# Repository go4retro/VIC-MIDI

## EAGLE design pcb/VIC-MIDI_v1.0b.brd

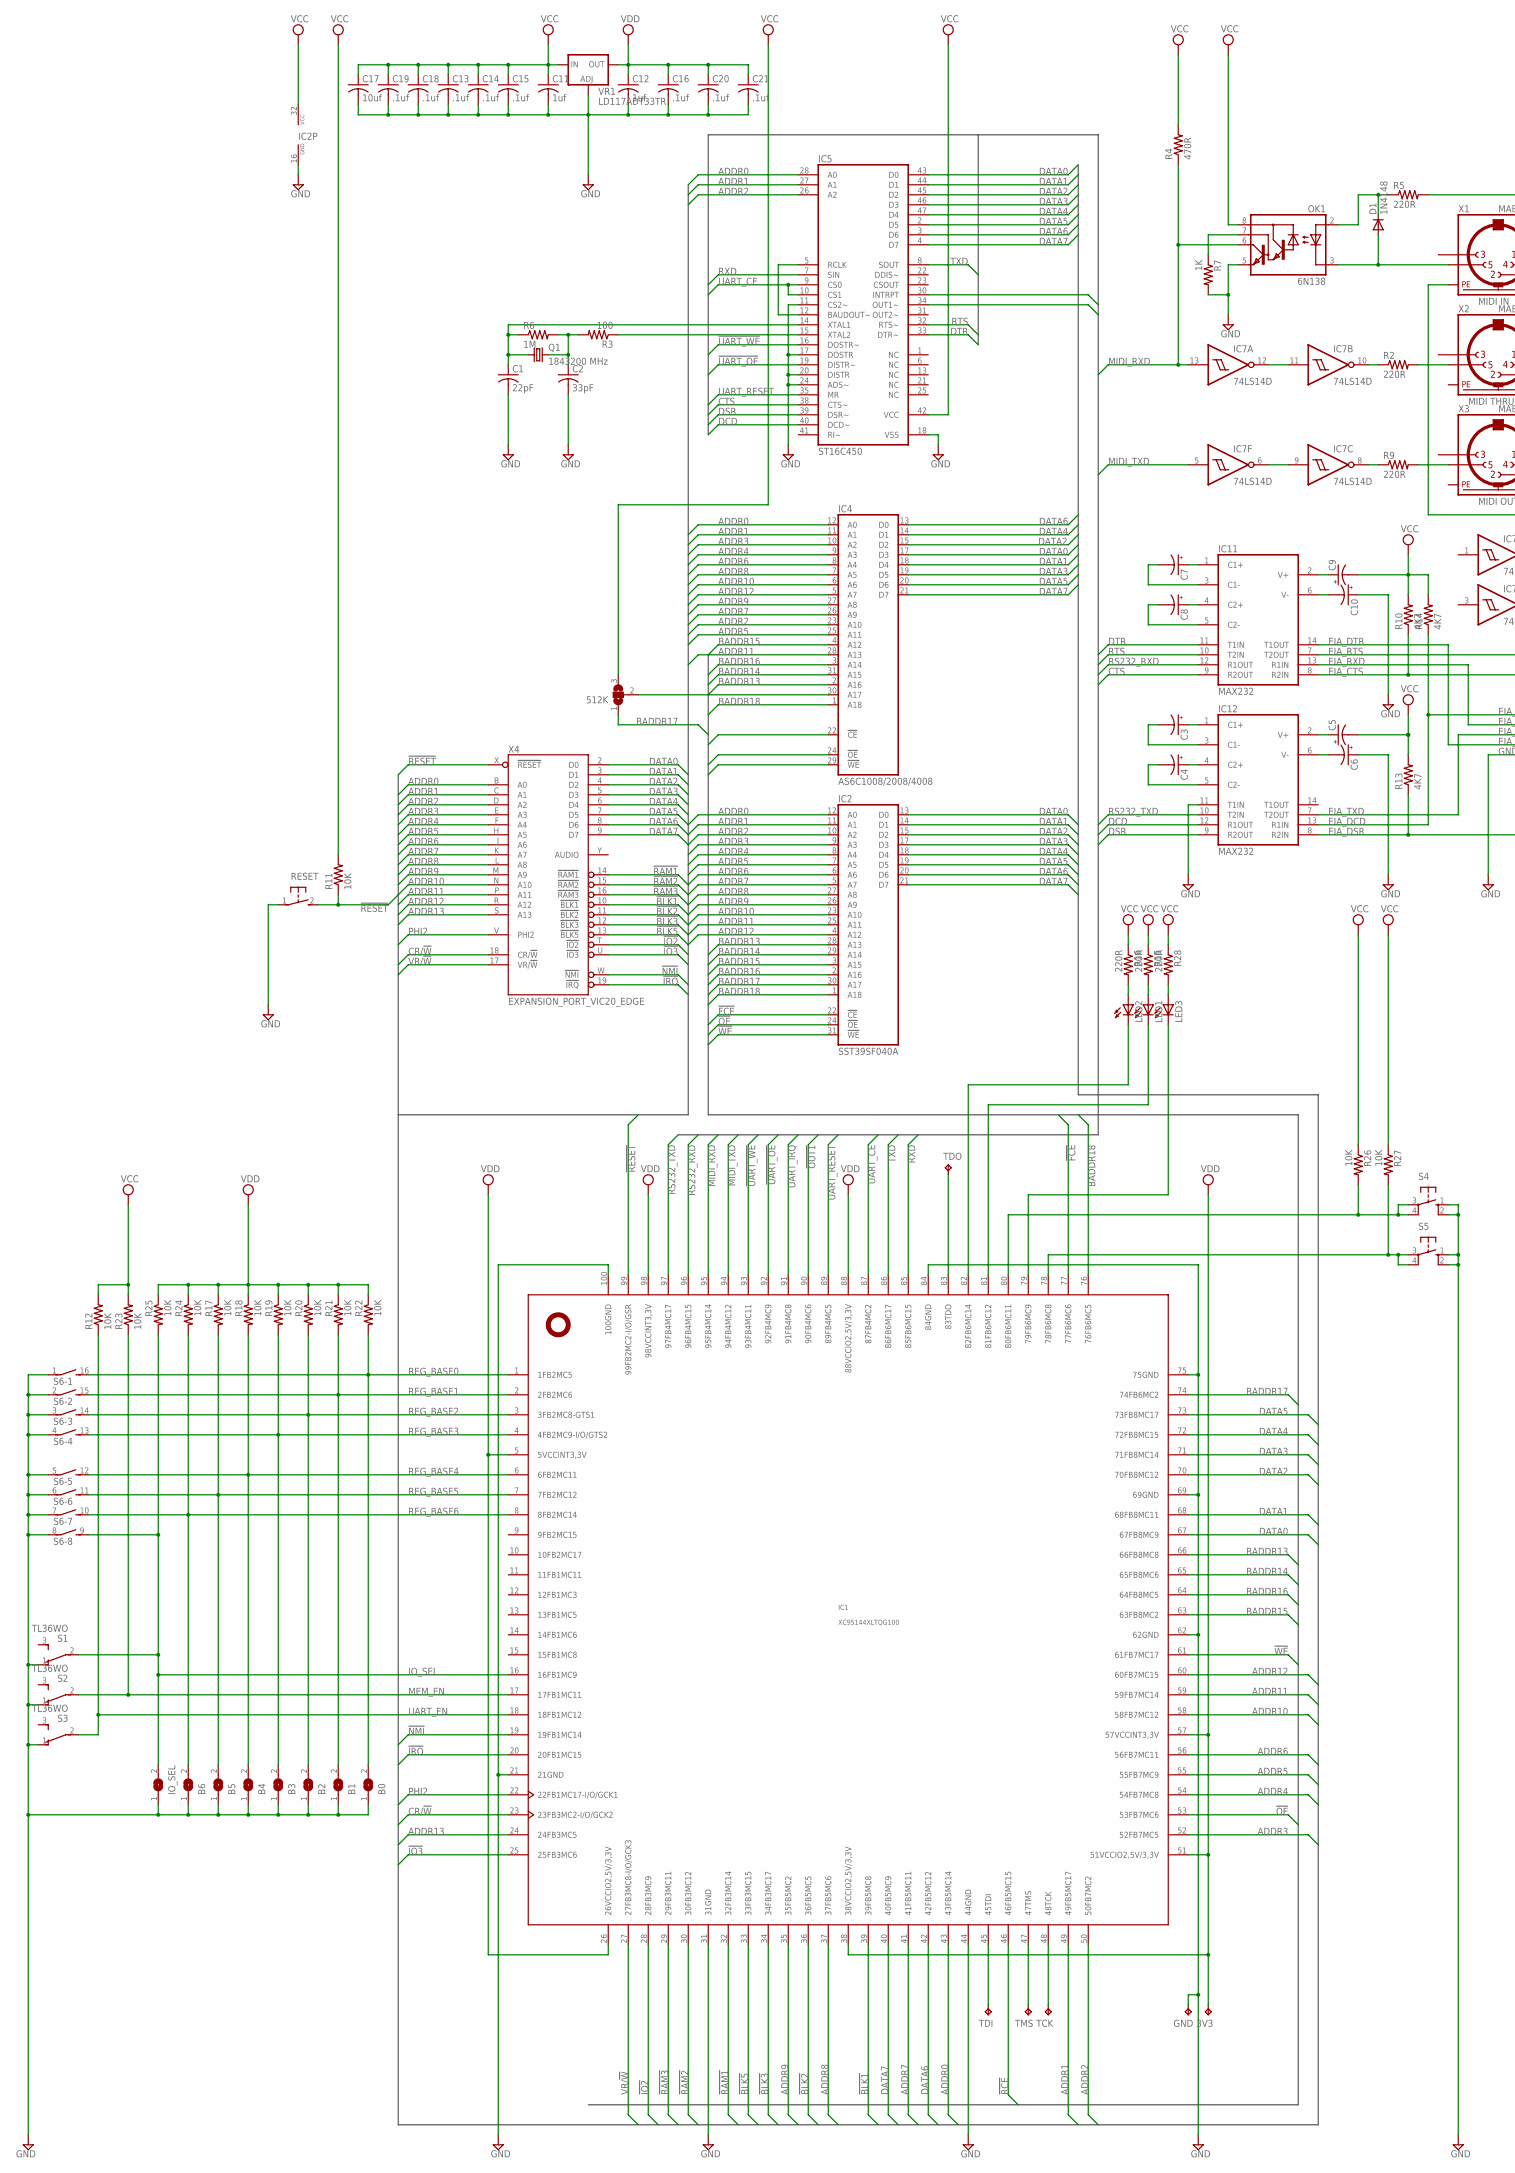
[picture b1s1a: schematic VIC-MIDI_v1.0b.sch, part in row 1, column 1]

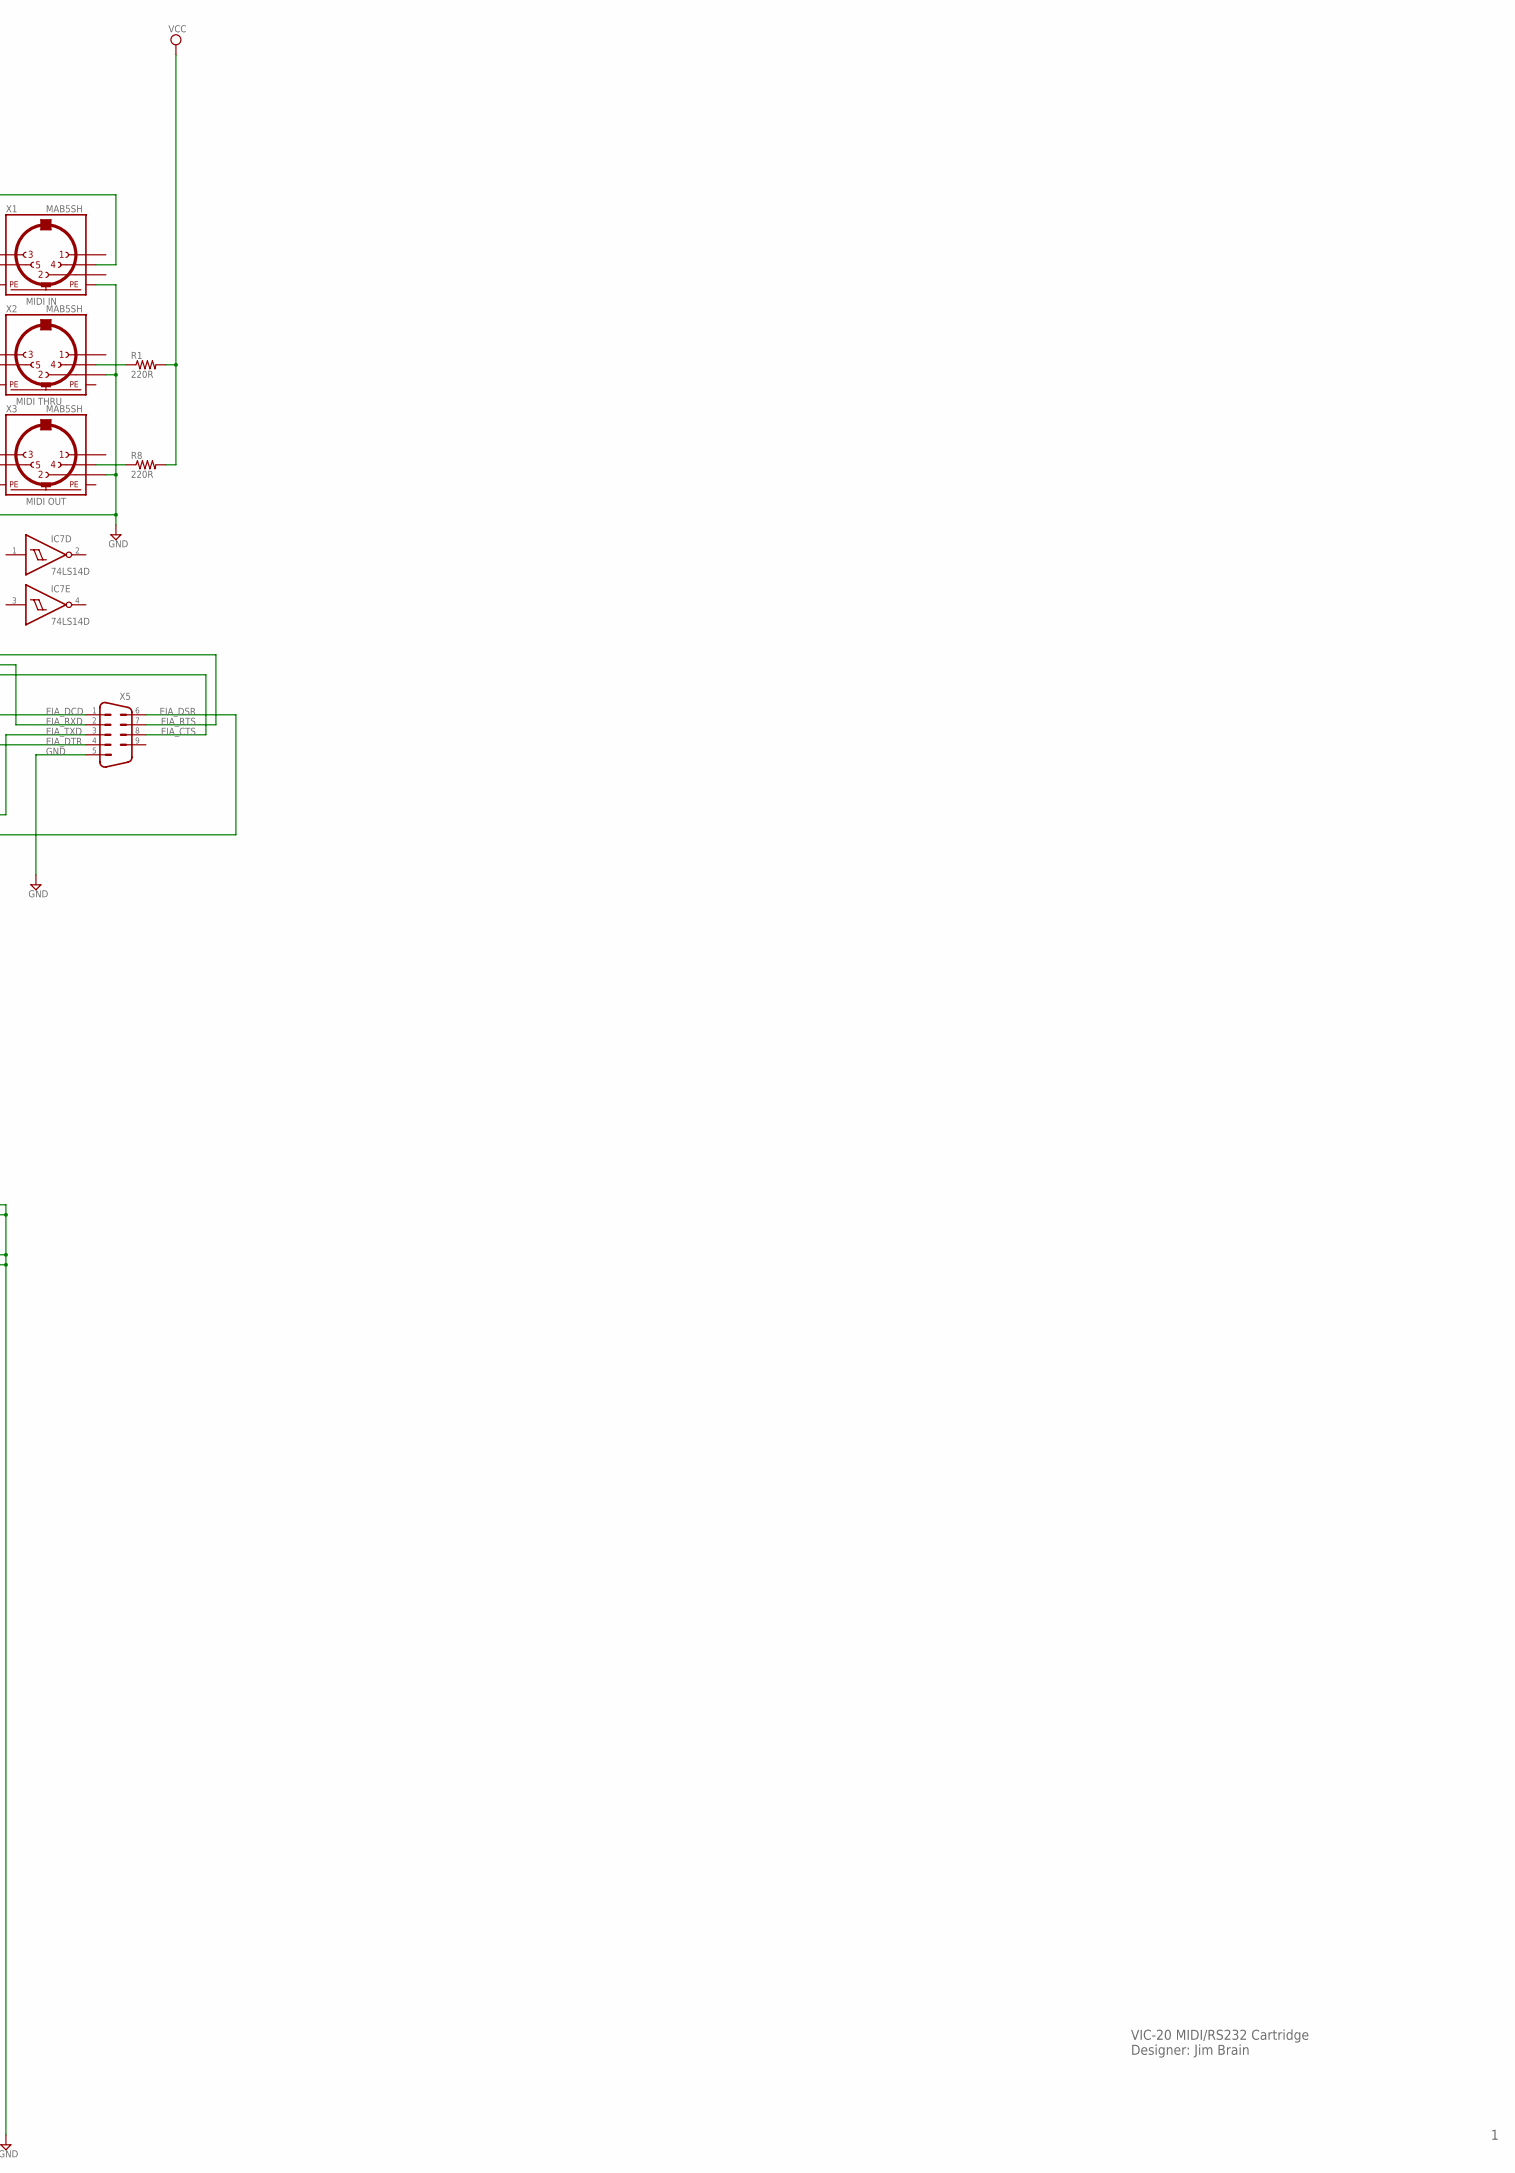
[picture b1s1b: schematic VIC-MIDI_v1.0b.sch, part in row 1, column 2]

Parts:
3V3: TPTP08R; TP08R
512K: SJ2W; SJ_2
B0, B1, B2, B3, B4, B5, B6: SJ
C1: 22pF; C0402
C2: 33pF; C0402
C3, C4, C5, C6, C7, C8, C9, C10: CPOL-USE2-4; E2-4
C11, C12: 1uf; C0402
C13, C14, C15, C16, C18, C19, C20, C21: .1uf; C0402
C17: 10uf; C0402
D1: 1N4148; DO35-7
GND: TPTP08R; TP08R
IC1: XC95144XLTQG100; TQFP100
IC2: SST39SF040A; PLCC32R
IC4: AS6C1008/2008/4008; SOP32L
IC5: ST16C450; TQFP48
IC7: 74LS14D; SO14
IC11, IC12: MAX232; DIL16
IO_SEL: SJ
LED1, LED2, LED3: LED3MM
OK1: 6N138; DIL08
Q1: 1843200 MHz; HC49UP
R1, R2, R5, R8, R9, R15, R16, R28: 220R; R0402
R3: 100; R0402
R4: 470R; R0402
R6: 1M; R0402
R7: 1K; R0402
R10, R13, R14: 4K7; R0402
R11, R12, R17, R18, R19, R20, R21, R22, R23, R24, R25, R26, R27: 10K; R0402
RESET: 31-XX; B3F-31XX
S1, S2, S3: TL36WO; TL3XWO
S4, S5: 10-XX; B3F-10XX
S6: DIP08SB
TCK: TPTP08R; TP08R
TDI: TPTP08R; TP08R
TDO: TPTP08R; TP08R
TMS: TPTP08R; TP08R
VR1: LD117ADT33TR; DPACK
X1, X2, X3: MAB5SH
X4: EXPANSION_PORT_VIC20_EDGE; MA156-22-2
X5: M09HP

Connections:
!BLK1: IC1.39 (39FB5MC8), X4.10 (!BLK1)
!BLK2: IC1.36 (36FB5MC5), X4.11 (!BLK2)
!BLK3: IC1.34 (34FB3MC17), X4.12 (!BLK3)
!BLK5: IC1.33 (33FB3MC15), X4.13 (!BLK5)
!FCE: IC1.77 (77FB6MC6), IC2.22 (!CE)
!IO2: IC1.28 (28FB3MC9), X4.T (!IO2)
!IO3: IC1.25 (25FB3MC6), X4.U (!IO3)
!IRQ: IC1.20 (20FB1MC15), X4.19 (!IRQ)
!NMI: IC1.19 (19FB1MC14), X4.W (!NMI)
!OE: IC1.53 (53FB7MC6), IC2.24 (!OE), IC4.24 (!OE)
!OUT1: IC1.90 (90FB4MC6), IC5.34 (OUT1~)
!RAM1: IC1.32 (32FB3MC14), X4.14 (!RAM1)
!RAM2: IC1.30 (30FB3MC12), X4.15 (!RAM2)
!RAM3: IC1.29 (29FB3MC11), X4.16 (!RAM3)
!RCE: IC1.46 (46FB5MC15), IC4.22 (!CE)
!RESET: IC1.99 (99FB2MC2-I/O/GSR), R11.1, RESET.2 (S), X4.X (!RESET)
!UART_OE: IC1.92 (92FB4MC9), IC5.19 (DISTR~)
!UART_WE: IC1.93 (93FB4MC11), IC5.16 (DOSTR~)
!WE: IC1.61 (61FB7MC17), IC2.31 (!WE), IC4.29 (!WE)
ADDR0: IC1.43 (43FB5MC14), IC2.12 (A0), IC4.12 (A0), IC5.28 (A0), X4.B (A0)
ADDR1: IC1.49 (49FB5MC17), IC2.11 (A1), IC4.11 (A1), IC5.27 (A1), X4.C (A1)
ADDR2: IC1.50 (50FB7MC2), IC2.10 (A2), IC4.23 (A10), IC5.26 (A2), X4.D (A2)
ADDR3: IC1.52 (52FB7MC5), IC2.9 (A3), IC4.10 (A2), X4.E (A3)
ADDR4: IC1.54 (54FB7MC8), IC2.8 (A4), IC4.9 (A3), X4.F (A4)
ADDR5: IC1.55 (55FB7MC9), IC2.7 (A5), IC4.25 (A11), X4.H (A5)
ADDR6: IC1.56 (56FB7MC11), IC2.6 (A6), IC4.8 (A4), X4.J (A6)
ADDR7: IC1.41 (41FB5MC11), IC2.5 (A7), IC4.26 (A9), X4.K (A7)
ADDR8: IC1.37 (37FB5MC6), IC2.27 (A8), IC4.7 (A5), X4.L (A8)
ADDR9: IC1.35 (35FB5MC2), IC2.26 (A9), IC4.27 (A8), X4.M (A9)
ADDR10: IC1.58 (58FB7MC12), IC2.23 (A10), IC4.6 (A6), X4.N (A10)
ADDR11: IC1.59 (59FB7MC14), IC2.25 (A11), IC4.28 (A13), X4.P (A11)
ADDR12: IC1.60 (60FB7MC15), IC2.4 (A12), IC4.5 (A7), X4.R (A12)
ADDR13: IC1.24 (24FB3MC5), X4.S (A13)
BADDR13: IC1.66 (66FB8MC8), IC2.28 (A13), IC4.2 (A16)
BADDR14: IC1.65 (65FB8MC6), IC2.29 (A14), IC4.31 (A15)
BADDR15: IC1.63 (63FB8MC2), IC2.3 (A15), IC4.4 (A12)
BADDR16: IC1.64 (64FB8MC5), IC2.2 (A16), IC4.3 (A14)
BADDR17: 512K.1, IC1.74 (74FB6MC2), IC2.30 (A17)
BADDR18: IC1.76 (76FB6MC5), IC2.1 (A18), IC4.1 (A18)
CR/!W: IC1.23 (23FB3MC2-I/O/GCK2), X4.18 (CR/!W)
CTS: IC5.38 (CTS~), IC11.9 (R2OUT)
DATA0: IC1.67 (67FB8MC9), IC2.13 (D0), IC4.17 (D3), IC5.43 (D0), X4.2 (D0)
DATA1: IC1.68 (68FB8MC11), IC2.14 (D1), IC4.18 (D4), IC5.44 (D1), X4.3 (D1)
DATA2: IC1.70 (70FB8MC12), IC2.15 (D2), IC4.15 (D2), IC5.45 (D2), X4.4 (D2)
DATA3: IC1.71 (71FB8MC14), IC2.17 (D3), IC4.19 (D5), IC5.46 (D3), X4.5 (D3)
DATA4: IC1.72 (72FB8MC15), IC2.18 (D4), IC4.14 (D1), IC5.47 (D4), X4.6 (D4)
DATA5: IC1.73 (73FB8MC17), IC2.19 (D5), IC4.20 (D6), IC5.2 (D5), X4.7 (D5)
DATA6: IC1.42 (42FB5MC12), IC2.20 (D6), IC4.13 (D0), IC5.3 (D6), X4.8 (D6)
DATA7: IC1.40 (40FB5MC9), IC2.21 (D7), IC4.21 (D7), IC5.4 (D7), X4.9 (D7)
DCD: IC5.40 (DCD~), IC12.12 (R1OUT)
DSR: IC5.39 (DSR~), IC12.9 (R2OUT)
DTR: IC5.33 (DTR~), IC11.11 (T1IN)
EIA_CTS: IC11.8 (R2IN), R10.1, X5.8
EIA_DCD: IC12.13 (R1IN), R14.1, X5.1
EIA_DSR: IC12.8 (R2IN), R13.1, X5.6
EIA_DTR: IC11.14 (T1OUT), X5.4
EIA_RTS: IC11.7 (T2OUT), X5.7
EIA_RXD: IC11.13 (R1IN), X5.2
EIA_TXD: IC12.7 (T2OUT), X5.3
GND: B0.1, B1.1, B2.1, B3.1, B4.1, B5.1, B6.1, C1.2, C2.2, C6.+, C10.+, C11.2, C12.2, C13.2, C14.2, C15.2, C16.2, C17.2, C18.2, C19.2, C20.2, C21.2, GND.TP, IC1.21 (21GND), IC1.31 (31GND), IC1.44 (44GND), IC1.62 (62GND), IC1.69 (69GND), IC1.75 (75GND), IC1.84 (84GND), IC1.100 (100GND), IC2.16 (GND), IC4.16 (GND), IC5.11 (CS2~), IC5.17 (DOSTR), IC5.18 (VSS), IC5.20 (DISTR), IC5.24 (ADS~), IC7.7 (GND), IC11.15 (GND), IC12.11 (T1IN), IC12.15 (GND), IO_SEL.1, OK1.5 (GND), R7.2, RESET.1, S1.1 (O), S2.1 (O), S3.1 (O), S4.1 (S), S4.2 (S1), S5.1 (S), S5.2 (S1), S6.1, S6.2 (1), S6.3 (1), S6.4 (1), S6.5 (1), S6.6 (1), S6.7 (1), S6.8 (1), VR1.1 (ADJ), X1.PE, X1.PE@ (PE), X2.2, X3.2, X4.1 (GND), X4.22 (GND), X4.A (GND), X4.Z (GND), X5.5
IO_SEL: IC1.16 (16FB1MC9), IO_SEL.2, R25.2, S1.2, S6.9 (2)
MEM_EN: IC1.17 (17FB1MC11), R23.1, S2.2
MIDI_RXD: IC1.95 (95FB4MC14), IC7.13 (I), OK1.6 (VO), R4.1
MIDI_TXD: IC1.94 (94FB4MC12), IC7.5 (I)
unnamed: R9.2, X3.5
unnamed: IC7.6 (O), IC7.9 (I)
unnamed: R8.1, X3.4
unnamed: IC7.8 (O), R9.1
unnamed: LED1.A, R15.2
unnamed: D1.C, OK1.2 (A), R5.1
unnamed: R5.2, X1.4
unnamed: D1.A, OK1.3 (C), X1.5
unnamed: OK1.7 (VB), R7.1
unnamed: R2.2, X2.5
unnamed: IC7.10 (O), R2.1
unnamed: IC7.11 (I), IC7.12 (O)
unnamed: R1.1, X2.4
unnamed: IC1.78 (78FB6MC8), R27.2, S5.3, S5.4 (P1)
unnamed: IC5.15 (XTAL2), R3.1
unnamed: C1.1, IC5.14 (XTAL1), Q1.1, R6.1
unnamed: C2.1, Q1.2, R3.2, R6.2
unnamed: IC1.81 (81FB6MC12), LED1.K (C)
unnamed: IC5.5 (RCLK), IC5.12 (BAUDOUT~)
unnamed: IC1.80 (80FB6MC11), R26.2, S4.3, S4.4 (P1)
unnamed: IC1.82 (82FB6MC14), LED2.K (C)
unnamed: LED3.A, R28.2
unnamed: IC1.79 (79FB6MC9), LED3.K (C)
unnamed: LED2.A, R16.2
unnamed: IC1.48 (48TCK), TCK.TP
unnamed: IC1.47 (47TMS), TMS.TP
unnamed: IC1.45 (45TDI), TDI.TP
unnamed: IC1.83 (83TDO), TDO.TP
unnamed: C3.+, IC12.1 (C1+)
unnamed: C3.-, IC12.3 (C1-)
unnamed: C4.+, IC12.4 (C2+)
unnamed: C4.-, IC12.5 (C2-)
unnamed: C5.+, IC12.2 (V+)
unnamed: C6.-, IC12.6 (V-)
unnamed: C7.+, IC11.1 (C1+)
unnamed: C7.-, IC11.3 (C1-)
unnamed: C8.+, IC11.4 (C2+)
unnamed: C8.-, IC11.5 (C2-)
unnamed: C9.+, IC11.2 (V+)
unnamed: C10.-, IC11.6 (V-)
unnamed: 512K.2, IC4.30 (A17)
PE: X2.PE, X2.PE@ (PE), X3.PE, X3.PE@ (PE)
PHI2: IC1.22 (22FB1MC17-I/O/GCK1), X4.V (PHI2)
REG_BASE0: B0.2, IC1.1 (1FB2MC5), R22.2, S6.16 (2)
REG_BASE1: B1.2, IC1.2 (2FB2MC6), R21.2, S6.15 (2)
REG_BASE2: B2.2, IC1.3 (3FB2MC8-GTS1), R20.2, S6.14 (2)
REG_BASE3: B3.2, IC1.4 (4FB2MC9-I/O/GTS2), R19.2, S6.13 (2)
REG_BASE4: B4.2, IC1.6 (6FB2MC11), R18.2, S6.12 (2)
REG_BASE5: B5.2, IC1.7 (7FB2MC12), R17.2, S6.11 (2)
REG_BASE6: B6.2, IC1.8 (8FB2MC14), R24.2, S6.10 (2)
RS232_RXD: IC1.96 (96FB4MC15), IC11.12 (R1OUT)
RS232_TXD: IC1.97 (97FB4MC17), IC12.10 (T2IN)
RTS: IC5.32 (RTS~), IC11.10 (T2IN)
RXD: IC1.85 (85FB6MC15), IC5.7 (SIN)
TXD: IC1.86 (86FB6MC17), IC5.8 (SOUT)
UART_CE: IC1.87 (87FB4MC2), IC5.9 (CS0), IC5.10 (CS1)
UART_EN: IC1.18 (18FB1MC12), R12.1, S3.2
UART_IRQ: IC1.91 (91FB4MC8), IC5.30 (INTRPT)
UART_RESET: IC1.89 (89FB4MC5), IC5.35 (MR)
VCC: 512K.3, C5.-, C9.-, C11.1, C13.1, C14.1, C15.1, C17.1, C18.1, C19.1, IC2.32 (VCC), IC4.32 (VCC), IC5.42 (VCC), IC7.14 (VCC), IC11.16 (VCC), IC12.16 (VCC), OK1.8 (VCC), R1.2, R4.2, R8.2, R10.2, R11.2, R12.2, R13.2, R14.2, R15.1, R16.1, R23.2, R26.1, R27.1, R28.1, VR1.3 (IN), X4.21 (VCC)
VDD: 3V3.TP, C12.1, C16.1, C20.1, C21.1, IC1.5 (5VCCINT3,3V), IC1.26 (26VCCIO2,5V/3,3V), IC1.38 (38VCCIO2,5V/3,3V), IC1.51 (51VCCIO2,5V/3,3V), IC1.57 (57VCCINT3,3V), IC1.88 (88VCCIO2,5V/3,3V), IC1.98 (98VCCINT3,3V), R17.1, R18.1, R19.1, R20.1, R21.1, R22.1, R24.1, R25.1, VR1.4 (OUT)
VR/!W: IC1.27 (27FB3MC8-I/O/GCK3), X4.17 (VR/!W)

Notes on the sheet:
Designer: Jim Brain
VIC-20 MIDI/RS232 Cartridge
MIDI OUT
MIDI IN
MIDI THRU

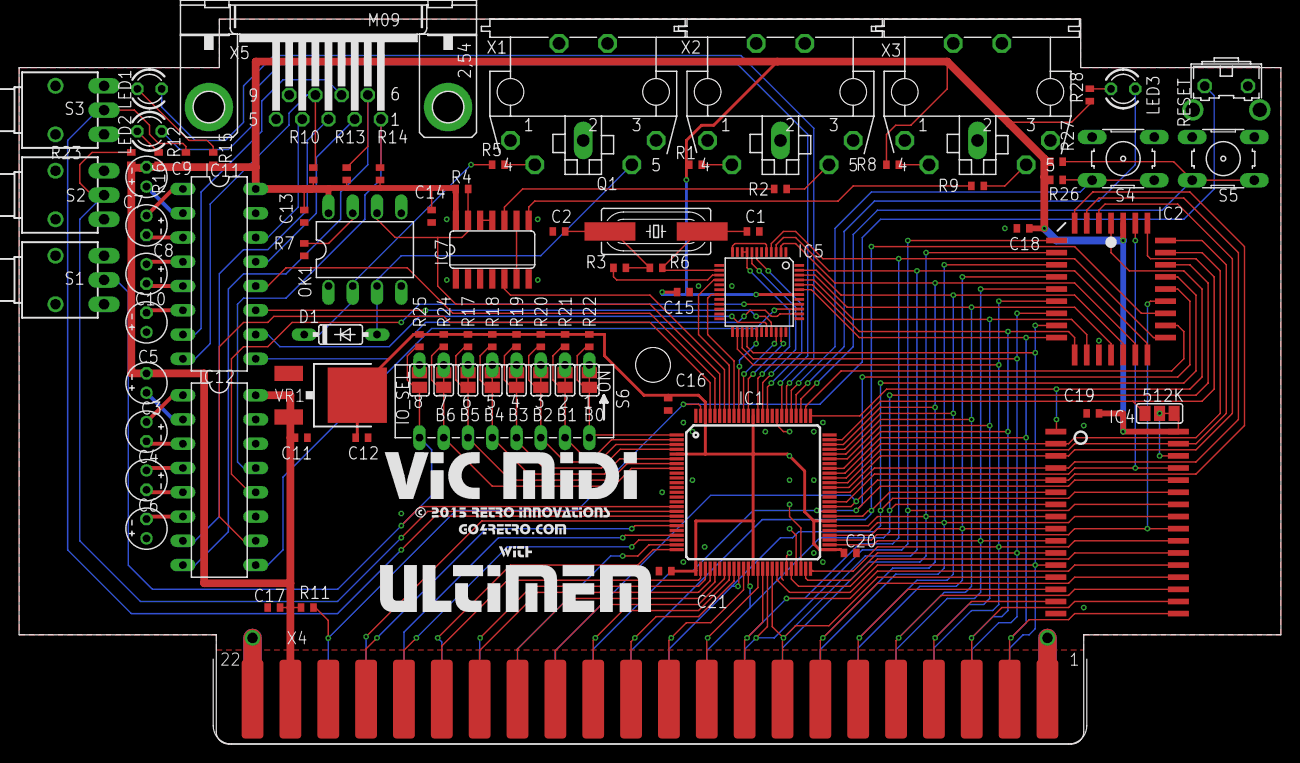
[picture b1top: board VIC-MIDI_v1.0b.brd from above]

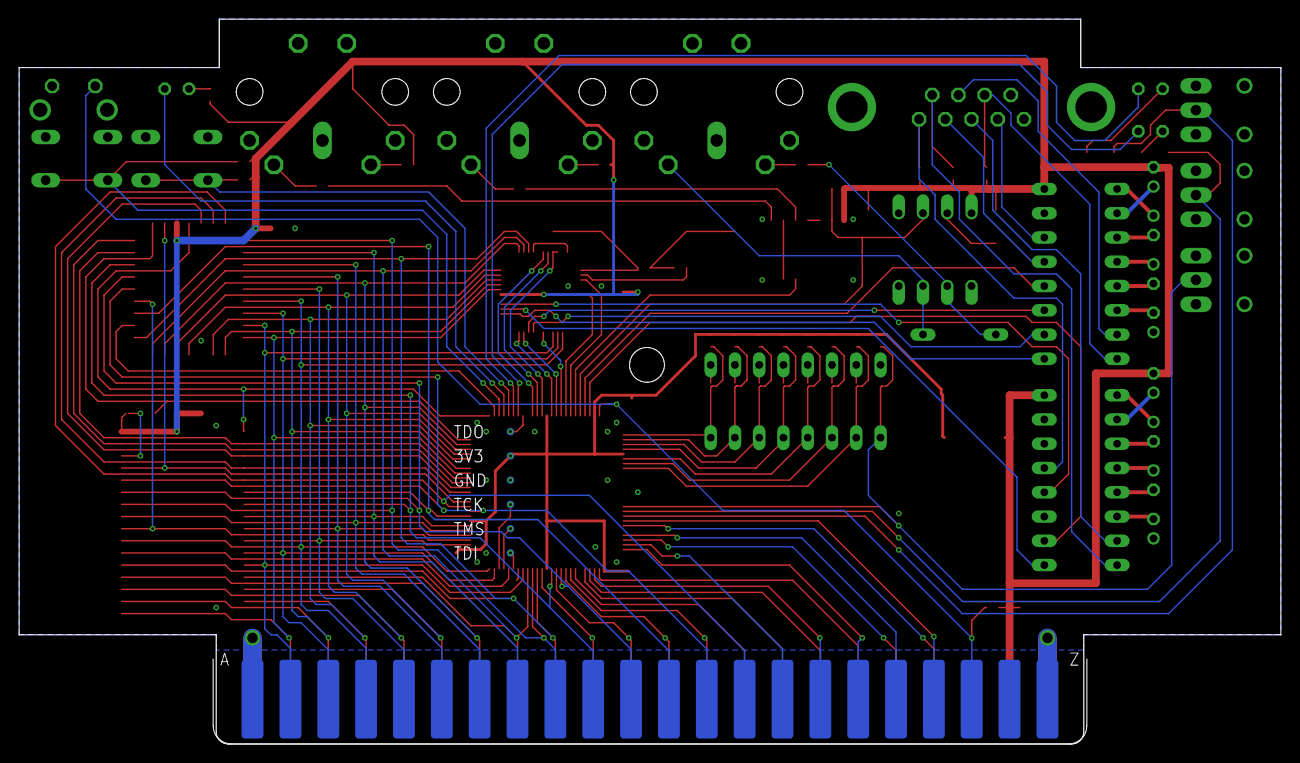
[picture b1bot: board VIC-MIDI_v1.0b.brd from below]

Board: 2 copper layers, 132.1 x 75.9 mm, 90 parts (6 on the bottom side), 126 nets.

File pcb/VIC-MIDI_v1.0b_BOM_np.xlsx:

| Legend | Quantity | Value | Part Number | Package
UltiMem
 | VR1 | 1 | 3.3V LDO VR | LD117ADT33TR
 | IC2 | 1 | 512kBx8 ROM | AM29F040B | TSOP48
 | IC1 | 1 | XC95144XLTQ100 | XC95144XL-TQ100 | TQFP100
 | IC3 | 1 | 128kBx8 RAM | KM68100BLG-7L | TSOP32
 | C11,C12 | 1 | 1uf | C-USC0402 | C0805
 | C17 | 2 | 10uf | C-USC0402 | C0805
 | C13,C14,C15,C16,C18,C19,C20,C21 | 8 | .1uf | C-USC0402 | C0805
 | RESET | 1 |  | 31-XX | B3F-31XX
 | S1,S2 | 2 | TL36WO | TL36WO | TL3XWO
 | S4,S5 | 2
 | IC5 | 1 | ST16C450 | XR-16C450Q | TQFP48
 | Q1 | 1 | 1843200 MHz | CRYSTALHC49UP | HC49UP
 | LED1 | 1 | red | LED3MM
 | LED2 | 1 | yellow | LED3MM
 | LED3 | 1 | green | LED3MM | LED3MM
 | C1 | 1 | 22pF | C-USC0402 | C0805
 | C2 | 1 | 33pF | C-USC0402 | C0805
 | R3 | 1 | 100 | R-US_R0402 | R0805
 | R6 | 1 | 1M | R-US_R0402 | R0805
 | R15,R16,R28 | 3 | 220R | R-US_R0402 | R0805
 | R11,R12,R17-R25 | 11 | 10K | R-US_R0402 | M0805
MIDI
 | D1 | 1 | 1N4148 | 1N4148DO35-7 | DO35-7
 | IC7 | 1 | 74HCT14 | 74HCT14 | SO14
 | OK1 | 1 | 6N138 | 6N138 | DIL08
 | X1-X3 | 3 | DIN5 | SDS-50J | MAB5SH
 | R1,R2,R5,R8,R9 | 5 | 220R | R-US_R0402 | R0805
 | R4 | 1 | 470R | R-US_R0402 | R0805
 | R7 | 1 | 1K | R-US_R0402 | R0805
RS232
 | IC11,IC12 | 2 | MAX232 | MAX232 | DIL16
 | C3-C10 | 8 | 1uF | CPOL-USE2-4 | E2-4
 | X4 | 1 | DE-9 M | 1-1634580-2 | F09HP
 | R10,R13,R14 | 3 | 4K7 | R-US_R0402 | R0805

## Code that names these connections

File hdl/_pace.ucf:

#PACE: Start of Constraints generated by PACE

#PACE: Start of PACE I/O Pin Assignments
NET "act_led"  LOC = "P79"  ; 
NET "address<0>"  LOC = "P43"  ; 
NET "address<1>"  LOC = "P49"  ; 
NET "address<2>"  LOC = "P50"  ; 
NET "address<3>"  LOC = "P52"  ; 
NET "address<4>"  LOC = "P54"  ; 
NET "address<5>"  LOC = "P55"  ; 
NET "address<6>"  LOC = "P56"  ; 
NET "address<7>"  LOC = "P41"  ; 
NET "address<8>"  LOC = "P37"  ; 
NET "address<9>"  LOC = "P35"  ; 
NET "bank<13>"  LOC = "P66"  ; 
NET "bank<14>"  LOC = "P65"  ; 
NET "bank<15>"  LOC = "P63"  ; 
NET "bank<16>"  LOC = "P64"  ; 
NET "bank<17>"  LOC = "P74"  ; 
NET "bank<18>"  LOC = "P76"  ; 
NET "base<0>"  LOC = "P1"  ; 
NET "base<1>"  LOC = "P2"  ; 
NET "base<2>"  LOC = "P3"  ; 
NET "base<3>"  LOC = "P4"  ; 
NET "base<4>"  LOC = "P6"  ; 
NET "base<5>"  LOC = "P7"  ; 
NET "base<6>"  LOC = "P8"  ; 
NET "blk1"  LOC = "P39"  ; 
NET "blk2"  LOC = "P36"  ; 
NET "blk3"  LOC = "P34"  ; 
NET "blk5"  LOC = "P33"  ; 
NET "clock"  LOC = "P22"  ; 
NET "data<0>"  LOC = "P67"  ; 
NET "data<1>"  LOC = "P68"  ; 
NET "data<2>"  LOC = "P70"  ; 
NET "data<3>"  LOC = "P71"  ; 
NET "data<4>"  LOC = "P72"  ; 
NET "data<5>"  LOC = "P73"  ; 
NET "data<6>"  LOC = "P42"  ; 
NET "data<7>"  LOC = "P40"  ; 
NET "flash_ce"  LOC = "P77"  ; 
NET "io<2>"  LOC = "P28"  ; 
NET "io<3>"  LOC = "P25"  ; 
NET "io_sel"  LOC = "P16"  ; 
NET "irq"  LOC = "P20"  ; 
NET "mem_en"  LOC = "P17"  ; 
NET "midi_rxd"  LOC = "P95"  ; 
NET "midi_txd"  LOC = "P94"  ; 
NET "nmi"  LOC = "P19"  ; 
NET "oe"  LOC = "P53"  ; 
NET "r_w"  LOC = "P23"  ; 
NET "ram1"  LOC = "P32"  ; 
NET "ram2"  LOC = "P30"  ; 
NET "ram3"  LOC = "P29"  ; 
NET "ram_ce"  LOC = "P46"  ; 
NET "reset"  LOC = "P99"  ; 
NET "rs232_rxd"  LOC = "P96"  ; 
NET "rs232_txd"  LOC = "P97"  ; 
NET "rxd"  LOC = "P85"  ; 
NET "rxd_led"  LOC = "P81"  ;
NET "ser_sel"  LOC = "P90"  ; 
NET "switch<0>"  LOC = "P78"  ; 
NET "switch<1>"  LOC = "P80"  ; 
NET "txd"  LOC = "P86"  ; 
NET "txd_led"  LOC = "P82"  ;
NET "uart_ce"  LOC = "P87"  ; 
NET "uart_en"  LOC = "P18"  ; 
NET "uart_irq"  LOC = "P91"  ; 
NET "uart_oe"  LOC = "P92"  ; 
NET "uart_reset"  LOC = "P89"  ; 
NET "uart_we"  LOC = "P93"  ; 
NET "we"  LOC = "P61"  ; 

#PACE: Start of PACE Area Constraints

#PACE: Start of PACE Prohibit Constraints

#PACE: End of Constraints generated by PACE

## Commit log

2018-05-06 Move mapping file to reference
2018-05-06 Verilog updates
2018-05-06 More Verilog updates
2018-05-06 Working Verilog
2018-05-06 Missing code
2018-05-06 Shipping Verilog Codebase
